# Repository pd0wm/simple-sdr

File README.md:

# simple-sdr PCB
Simple Software Defined Radio based on [Softrock Lite II](http://wb5rvz.org/softrock_lite_ii/index/projectId=8). The IF generation and sampling is handled by an STM32F042. This design is intended to build a low cost [NAVTEX](https://en.wikipedia.org/wiki/NAVTEX) receiver, but can be used for all kinds of purposes. The current design has an input bandpass filter ranging from 400 - 1600 KHz.

WARNING: So far I haven't been able to receive anything yet with this hardware. Please use at your own risk.

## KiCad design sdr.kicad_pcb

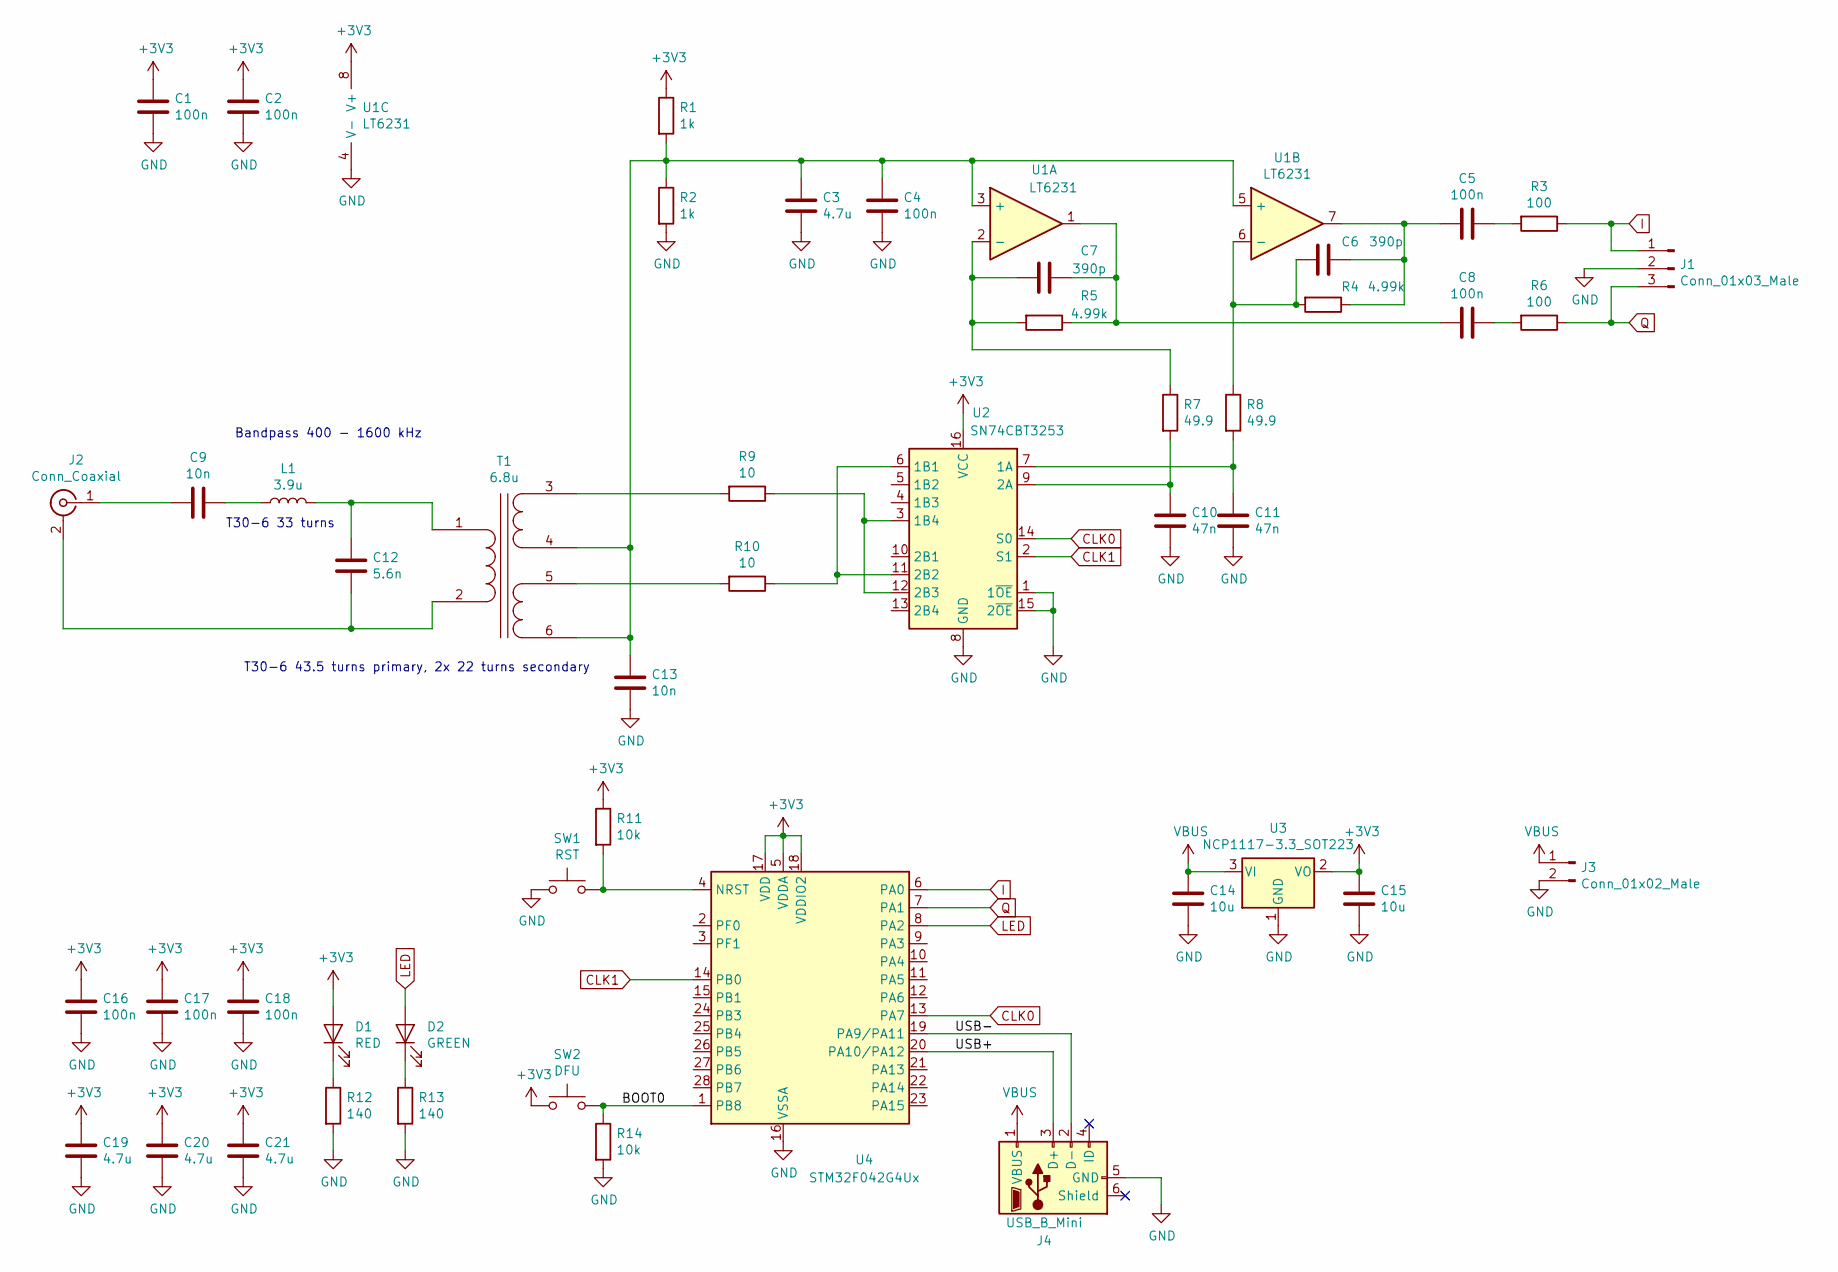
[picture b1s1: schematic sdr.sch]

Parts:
C1, C2, C4, C5, C8, C16, C17, C18: 100n; C_0603_1608Metric_Pad1.05x0.95mm_HandSolder; Digikey 399-1100-1-ND
C3, C19, C20, C21: 4.7u; C_0603_1608Metric_Pad1.05x0.95mm_HandSolder; Digikey 1276-1907-1-ND
C6, C7: 390p; C_0603_1608Metric_Pad1.05x0.95mm_HandSolder; Digikey 399-14983-1-ND
C9, C13: 10n; C_0603_1608Metric_Pad1.05x0.95mm_HandSolder; Digikey 399-7842-1-ND
C10, C11: 47n; C_0603_1608Metric_Pad1.05x0.95mm_HandSolder; Digikey 1276-1063-1-ND
C12: 5.6n; C_0603_1608Metric_Pad1.05x0.95mm_HandSolder; Digikey 1276-2091-1-ND
C14, C15: 10u; C_0603_1608Metric_Pad1.05x0.95mm_HandSolder; Digikey 490-13248-1-ND
D1: RED; LED_0603_1608Metric_Pad1.05x0.95mm_HandSolder; Digikey 732-4978-1-ND
D2: GREEN; LED_0603_1608Metric_Pad1.05x0.95mm_HandSolder; Digikey 732-4971-1-ND
J1: Conn_01x03_Male; PinHeader_1x03_P2.54mm_Vertical
J2: Conn_Coaxial; SMA_Amphenol_901-144_Vertical
J3: Conn_01x02_Male; PinHeader_1x02_P2.54mm_Vertical
J4: USB_B_Mini; USB_Mini-B_Wuerth_65100516121_Horizontal; Digikey 732-2109-1-ND
L1: 3.9u; PinHeader_1x02_P2.54mm_Vertical
R1, R2: 1k; R_0603_1608Metric_Pad1.05x0.95mm_HandSolder; Digikey 311-1.00KHRCT-ND
R3, R6: 100; R_0603_1608Metric_Pad1.05x0.95mm_HandSolder; Digikey 311-100HRCT-ND
R4, R5: 4.99k; R_0603_1608Metric_Pad1.05x0.95mm_HandSolder; Digikey 311-4.99KHRCT-ND
R7, R8: 49.9; R_0603_1608Metric_Pad1.05x0.95mm_HandSolder; Digikey 311-49.9HRCT-ND
R9, R10: 10; R_0603_1608Metric_Pad1.05x0.95mm_HandSolder; Digikey 311-10.0HRCT-ND
R11, R14: 10k; R_0603_1608Metric_Pad1.05x0.95mm_HandSolder; Digikey 311-10.0KHRCT-ND
R12, R13: 140; R_0603_1608Metric_Pad1.05x0.95mm_HandSolder; Digikey 311-140HRCT-ND
SW1: RST; SW_SPST_EVQQ2; Digikey P12932SCT-ND
SW2: DFU; SW_SPST_EVQQ2; Digikey P12932SCT-ND
T1: 6.8u; PinHeader_2x03_P2.54mm_Vertical
U1: LT6231; SOIC-8_3.9x4.9mm_P1.27mm; Digikey LT6231CS8#PBF-ND
U2: SN74CBT3253; SOIC-16_3.9x9.9mm_P1.27mm; Digikey 296-19206-1-ND
U3: NCP1117-3.3_SOT223; SOT-223-3_TabPin2; Digikey NCP1117LPST33T3GOSCT-ND
U4: STM32F042G4Ux; QFN-28_4x4mm_P0.5mm; Digikey 497-17830-ND

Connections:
+3V3: C1.1, C2.1, C15.1, C16.1, C17.1, C18.1, C19.1, C20.1, C21.1, D1.2 (A), R1.1, R11.1, SW2.1, U1.8 (V+), U2.16 (VCC), U3.2 (VO), U4.5 (VDDA), U4.17 (VDD), U4.18 (VDDIO2)
/BOOT0: R14.1, SW2.2, U4.1 (PB8)
/USB+: J4.3 (D+), U4.20 (PA10/PA12)
/USB-: J4.2 (D-), U4.19 (PA9/PA11)
CLK0: U2.14 (S0), U4.13 (PA7)
CLK1: U2.2 (S1), U4.14 (PB0)
GND: C1.2, C2.2, C3.2, C4.2, C10.2, C11.2, C13.2, C14.2, C15.2, C16.2, C17.2, C18.2, C19.2, C20.2, C21.2, J1.2, J3.2, J4.5 (GND), R2.2, R12.2, R13.2, R14.2, SW1.1, U1.4 (V-), U2.1 (1~OE), U2.8 (GND), U2.15 (2~OE), U3.1 (GND), U4.16 (VSSA)
I: J1.1, R3.1, U4.6 (PA0)
LED: D2.2 (A), U4.8 (PA2)
unnamed: C5.1, R3.2
unnamed: C5.2, C6.1, R4.1, U1.7
unnamed: C6.2, R4.2, R8.1, U1.6 (-)
unnamed: C7.1, C8.2, R5.1, U1.1
unnamed: C7.2, R5.2, R7.1, U1.2 (-)
unnamed: C8.1, R6.2
unnamed: C9.1, L1.1
unnamed: C9.2, J2.1 (In)
unnamed: C10.1, R7.2, U2.9 (2A)
unnamed: C11.1, R8.2, U2.7 (1A)
unnamed: C12.1, L1.2, T1.1 (AA)
unnamed: C12.2, J2.2 (Ext), T1.2 (AB)
unnamed: C3.1, C4.1, C13.1, R1.2, R2.1, T1.4 (SB), T1.6 (SD), U1.3 (+), U1.5 (+)
unnamed: D1.1 (K), R12.1
unnamed: D2.1 (K), R13.1
unnamed: R9.1, U2.3 (1B4), U2.12 (2B3)
unnamed: R9.2, T1.3 (SA)
unnamed: R10.1, U2.6 (1B1), U2.11 (2B2)
unnamed: R10.2, T1.5 (SC)
unnamed: R11.2, SW1.2, U4.4 (NRST)
Q: J1.3, R6.1, U4.7 (PA1)
VBUS: C14.1, J3.1, J4.1 (VBUS), U3.3 (VI)

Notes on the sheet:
T30-6 33 turns
T30-6 43.5 turns primary, 2x 22 turns secondary
Bandpass 400 - 1600 kHz

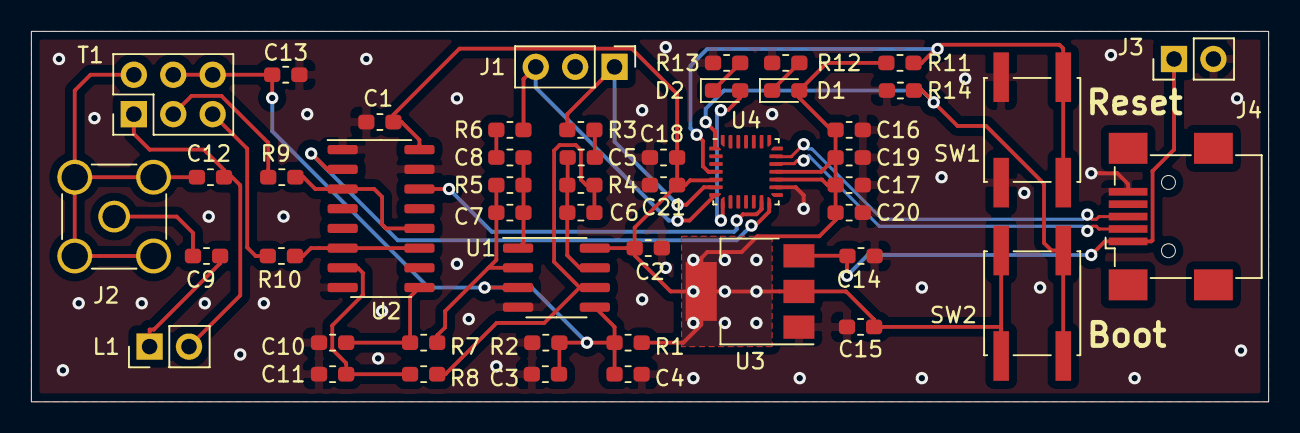
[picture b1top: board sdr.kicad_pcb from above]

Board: 2 copper layers, 79.8 x 23.9 mm, 49 parts (0 on the bottom side), 31 nets.

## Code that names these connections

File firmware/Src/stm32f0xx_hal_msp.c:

/* USER CODE BEGIN Header */
/**
  ******************************************************************************
  * File Name          : stm32f0xx_hal_msp.c
  * Description        : This file provides code for the MSP Initialization 
  *                      and de-Initialization codes.
  ******************************************************************************
  * @attention
  *
  * <h2><center>&copy; Copyright (c) 2020 STMicroelectronics.
  * All rights reserved.</center></h2>
  *
  * This software component is licensed by ST under BSD 3-Clause license,
  * the "License"; You may not use this file except in compliance with the
  * License. You may obtain a copy of the License at:
  *                        opensource.org/licenses/BSD-3-Clause
  *
  ******************************************************************************
  */
/* USER CODE END Header */

/* Includes ------------------------------------------------------------------*/
#include "main.h"
/* USER CODE BEGIN Includes */

/* USER CODE END Includes */

/* Private typedef -----------------------------------------------------------*/
/* USER CODE BEGIN TD */

/* USER CODE END TD */

/* Private define ------------------------------------------------------------*/
/* USER CODE BEGIN Define */
 
/* USER CODE END Define */

/* Private macro -------------------------------------------------------------*/
/* USER CODE BEGIN Macro */

/* USER CODE END Macro */

/* Private variables ---------------------------------------------------------*/
/* USER CODE BEGIN PV */

/* USER CODE END PV */

/* Private function prototypes -----------------------------------------------*/
/* USER CODE BEGIN PFP */

/* USER CODE END PFP */

/* External functions --------------------------------------------------------*/
/* USER CODE BEGIN ExternalFunctions */

/* USER CODE END ExternalFunctions */

/* USER CODE BEGIN 0 */

/* USER CODE END 0 */
                        
void HAL_TIM_MspPostInit(TIM_HandleTypeDef *htim);
                                        /**
  * Initializes the Global MSP.
  */
void HAL_MspInit(void)
{
  /* USER CODE BEGIN MspInit 0 */

  /* USER CODE END MspInit 0 */

  __HAL_RCC_SYSCFG_CLK_ENABLE();
  __HAL_RCC_PWR_CLK_ENABLE();

  /* System interrupt init*/

  /* USER CODE BEGIN MspInit 1 */

  /* USER CODE END MspInit 1 */
}

/**
* @brief ADC MSP Initialization
* This function configures the hardware resources used in this example
* @param hadc: ADC handle pointer
* @retval None
*/
void HAL_ADC_MspInit(ADC_HandleTypeDef* hadc)
{
  GPIO_InitTypeDef GPIO_InitStruct = {0};
  if(hadc->Instance==ADC1)
  {
  /* USER CODE BEGIN ADC1_MspInit 0 */

  /* USER CODE END ADC1_MspInit 0 */
    /* Peripheral clock enable */
    __HAL_RCC_ADC1_CLK_ENABLE();
  
    __HAL_RCC_GPIOA_CLK_ENABLE();
    /**ADC GPIO Configuration    
    PA0     ------> ADC_IN0
    PA1     ------> ADC_IN1 
    */
    GPIO_InitStruct.Pin = GPIO_PIN_0|GPIO_PIN_1;
    GPIO_InitStruct.Mode = GPIO_MODE_ANALOG;
    GPIO_InitStruct.Pull = GPIO_NOPULL;
    HAL_GPIO_Init(GPIOA, &GPIO_InitStruct);

  /* USER CODE BEGIN ADC1_MspInit 1 */

  /* USER CODE END ADC1_MspInit 1 */
  }

}

/**
* @brief ADC MSP De-Initialization
* This function freeze the hardware resources used in this example
* @param hadc: ADC handle pointer
* @retval None
*/
void HAL_ADC_MspDeInit(ADC_HandleTypeDef* hadc)
{
  if(hadc->Instance==ADC1)
  {
  /* USER CODE BEGIN ADC1_MspDeInit 0 */

  /* USER CODE END ADC1_MspDeInit 0 */
    /* Peripheral clock disable */
    __HAL_RCC_ADC1_CLK_DISABLE();
  
    /**ADC GPIO Configuration    
    PA0     ------> ADC_IN0
    PA1     ------> ADC_IN1 
    */
    HAL_GPIO_DeInit(GPIOA, GPIO_PIN_0|GPIO_PIN_1);

  /* USER CODE BEGIN ADC1_MspDeInit 1 */

  /* USER CODE END ADC1_MspDeInit 1 */
  }

}

/**
* @brief TIM_Base MSP Initialization
* This function configures the hardware resources used in this example
* @param htim_base: TIM_Base handle pointer
* @retval None
*/
void HAL_TIM_Base_MspInit(TIM_HandleTypeDef* htim_base)
{
  if(htim_base->Instance==TIM1)
  {
  /* USER CODE BEGIN TIM1_MspInit 0 */

  /* USER CODE END TIM1_MspInit 0 */
    /* Peripheral clock enable */
    __HAL_RCC_TIM1_CLK_ENABLE();
  /* USER CODE BEGIN TIM1_MspInit 1 */

  /* USER CODE END TIM1_MspInit 1 */
  }
  else if(htim_base->Instance==TIM2)
  {
  /* USER CODE BEGIN TIM2_MspInit 0 */

  /* USER CODE END TIM2_MspInit 0 */
    /* Peripheral clock enable */
    __HAL_RCC_TIM2_CLK_ENABLE();
  /* USER CODE BEGIN TIM2_MspInit 1 */

  /* USER CODE END TIM2_MspInit 1 */
  }

}

void HAL_TIM_MspPostInit(TIM_HandleTypeDef* htim)
{
  GPIO_InitTypeDef GPIO_InitStruct = {0};
  if(htim->Instance==TIM1)
  {
  /* USER CODE BEGIN TIM1_MspPostInit 0 */

  /* USER CODE END TIM1_MspPostInit 0 */
    __HAL_RCC_GPIOA_CLK_ENABLE();
    __HAL_RCC_GPIOB_CLK_ENABLE();
    /**TIM1 GPIO Configuration    
    PA7     ------> TIM1_CH1N
    PB0     ------> TIM1_CH2N 
    */
    GPIO_InitStruct.Pin = GPIO_PIN_7;
    GPIO_InitStruct.Mode = GPIO_MODE_AF_PP;
    GPIO_InitStruct.Pull = GPIO_NOPULL;
    GPIO_InitStruct.Speed = GPIO_SPEED_FREQ_HIGH;
    GPIO_InitStruct.Alternate = GPIO_AF2_TIM1;
    HAL_GPIO_Init(GPIOA, &GPIO_InitStruct);

    GPIO_InitStruct.Pin = GPIO_PIN_0;
    GPIO_InitStruct.Mode = GPIO_MODE_AF_PP;
    GPIO_InitStruct.Pull = GPIO_NOPULL;
    GPIO_InitStruct.Speed = GPIO_SPEED_FREQ_HIGH;
    GPIO_InitStruct.Alternate = GPIO_AF2_TIM1;
    HAL_GPIO_Init(GPIOB, &GPIO_InitStruct);

  /* USER CODE BEGIN TIM1_MspPostInit 1 */

  /* USER CODE END TIM1_MspPostInit 1 */
  }
  else if(htim->Instance==TIM2)
  {
  /* USER CODE BEGIN TIM2_MspPostInit 0 */

  /* USER CODE END TIM2_MspPostInit 0 */
  
    __HAL_RCC_GPIOA_CLK_ENABLE();
    /**TIM2 GPIO Configuration    
    PA2     ------> TIM2_CH3 
    */
    GPIO_InitStruct.Pin = GPIO_PIN_2;
    GPIO_InitStruct.Mode = GPIO_MODE_AF_PP;
    GPIO_InitStruct.Pull = GPIO_NOPULL;
    GPIO_InitStruct.Speed = GPIO_SPEED_FREQ_LOW;
    GPIO_InitStruct.Alternate = GPIO_AF2_TIM2;
    HAL_GPIO_Init(GPIOA, &GPIO_InitStruct);

  /* USER CODE BEGIN TIM2_MspPostInit 1 */

  /* USER CODE END TIM2_MspPostInit 1 */
  }

}
/**
* @brief TIM_Base MSP De-Initialization
* This function freeze the hardware resources used in this example
* @param htim_base: TIM_Base handle pointer
* @retval None
*/
void HAL_TIM_Base_MspDeInit(TIM_HandleTypeDef* htim_base)
{
  if(htim_base->Instance==TIM1)
  {
  /* USER CODE BEGIN TIM1_MspDeInit 0 */

  /* USER CODE END TIM1_MspDeInit 0 */
    /* Peripheral clock disable */
    __HAL_RCC_TIM1_CLK_DISABLE();
  /* USER CODE BEGIN TIM1_MspDeInit 1 */

  /* USER CODE END TIM1_MspDeInit 1 */
  }
  else if(htim_base->Instance==TIM2)
  {
  /* USER CODE BEGIN TIM2_MspDeInit 0 */

  /* USER CODE END TIM2_MspDeInit 0 */
    /* Peripheral clock disable */
    __HAL_RCC_TIM2_CLK_DISABLE();
  /* USER CODE BEGIN TIM2_MspDeInit 1 */

  /* USER CODE END TIM2_MspDeInit 1 */
  }

}

/* USER CODE BEGIN 1 */

/* USER CODE END 1 */

/************************ (C) COPYRIGHT STMicroelectronics *****END OF FILE****/

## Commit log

2020-05-06 add schematic picture
2020-05-07 add gerbers as ordered
2020-05-07 Create LICENSE
2020-05-14 connect missing wire
2020-05-14 move into folder
2020-05-14 add firmware
2020-05-21 led is blinking on timer
2020-05-21 HAL_TIMEx_OCN_Start was the solution
2020-05-21 517Khz output
2020-05-21 actual 90 degree phase shift
